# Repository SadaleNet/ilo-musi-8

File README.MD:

**(English: Scroll down for English | toki ike Inli li lon anpa pi toki pona)**

* lipu: https://ilomusi8.sadale.net/
* sitelen tawa lon ilo Jutu "Youtube": (TODO: tenpo ni la ona li lon ala. o awen a!)

# ilo musi 8 - ilo musi pi nasin CHIP-8

kepeken ilo musi 8 (ilo musi ali) la sina ken musi e musi CHIP-8. ilo musi 8 la:

* nasin CHIP-8 ni li ken:
	* nasin CHIP-8 (VIP) li ken
	* nasin SuperCHIP li ken
	* nasin XO-CHIP li ken lili. ni li ken ala: toki `plane n` (kule) en ma sona >= 4096. ali ante li ken
* tenpo pali: 5400 ips (90 instructions/frame)
* nena: nena CHIP-8 ali li lon (0-9, A-F). nena namako X kin li lon
* suli poki: 135x70x24mm
* wawa: poki wawa AAx2 anu linja wawa "USB MicroB"
* sona musi: kepeken lipu sona "TF Card"
	* nasin FAT16 en nasin FAT32 taso (o kepeken ala nasin exFAT!)
	* [nasin nimi "8.3 filename"](https://en.wikipedia.org/wiki/8.3_filename) taso
	* sina kin li ken pana e sona sin tawa ilo musi 8 kepeken lipu sona "TF Card"
* musi open li lon. sina pana e wawa tawa ilo musi 8 sina la sina ken lukin e sitelen pi wile sina
* toki mute li lon: toki pona (sitelen Lasin en sitelen pona) en [sitelen Sate](https://sadale.net/tok/sitelen-sate) en toki ike Inli
* sona ali ona li lon. jan ali li ken lukin e ona li ken ante e ona li ken pali e ona
* jan li ken pali e ona mute kepeken mani lili kepeken tenpo lili (sina pali e ona mute "20" la sina o pana e mani "$12x20" o kepeken tenpo "30minutesx20")
* jan li ken ante e lukin ona (jan li ken ante e musi open. jan li ken ante e sitelen lon selo.)

## sona seme li lon?

```
assembly/        # lon ma ni la sina kama sona e nasin pali pi ilo musi 8
bootloader/      # kepeken sona ni la sina ken pana e sona sin tawa ilo musi 8. ona li kama sona tan ILOMUSI8.BIN lon lipu sona
docs-assets/     # sitelen pi lipu README.MD
enclosure/       # sitelen pi lupa selo
firmware/        # kepeken sona ni la ilo musi 8 li pali. sina ken musi kepeken ilo musi 8 tan ni: sona ni li lon
kicad/           # lipu kiwen sona. ilo musi 8 li jo e lipu kiwen. jan li pana e sona tawa ona la ilo musi 8 li ken pali
label/           # sitelen selo en sitelen poki
manual/          # jan li lukin e ona la jan ni li kama sona e ilo musi 8 li ken musi kepeken ona
```

## o esun e ilo ni!

sina ken esun e ona lon [esun Sate](https://esun.sadale.net/)!

mi jo e mani namako la mi wile pana e ilo musi 8 tawa jan pi mani ala. :)

## o pali e ilo ni!

o lukin e lipu ni: "[assembly/](./assembly/)"

## ken

lipu anpa ni li mi ala. sina wile lukin e ken ona la o lukin e nimi insa ona:

* ./bootloader/linker_script
* ./bootloader/pff3a
* ./firmware/fatfs

mi pali e lipu ante ali. ken ona li ken "BSD 2-clause".

# ilo musi 8 - Handheld CHIP-8 Game Console

ilo musi 8 is a production-ready handheld CHIP-8 game console. Feature list:

* CHIP-8 Compatibility:
	* CHIP-8 (VIP): Full support
	* SuperCHIP: Full support
	* XO-CHIP: Partial support. No support for `plane n` (color mode) and memory beyond 4K. Everything else (e.g. audio) is fully supported
* Performance: 5400 ips (90 instructions/frame)
* Buttons: Full CHIP-8 button support (0-9, A-F), with an extra X key for escaping
* Dimensions: 135x70x24mm
* Power: AAx2 or USB MicroB
* Game Storage: TF card
	* Supports FAT16 and FAT32 (No support for exFAT)
	* Supports [8.3 filename](https://en.wikipedia.org/wiki/8.3_filename) only
	* Firmware update is supported via the card
* Bootrom support. Can be used for showing boot screen upon powering on of the device
* Multi-language UI: English, [Toki Pona](https://en.wikipedia.org/wiki/Toki_Pona) and [Sadalian Script](https://sadale.net/en/sadalian)
* Fully open source, including electronics, enclosure and firmware, with full BOM and assembly instruction.
* Optimized for small scale production in terms of material cost and box build assembly time (At batch of 20, it costs $12 and 30 minutes of assembly time per unit)
* Optimized for white-labeling (custom boot screen via the bootrom, custom branding sticker on enclosure, custom cardboard label, etc.)

## Repo Structure

```
assembly/        # Assembly instruction for you to build your own unit
bootloader/      # Bootloader for flashing the file "ILOMUSI8.BIN" on TF card as firmware
cardboard_label/ # Label slapped onto the packaging cardboard
docs-assets/     # Images for README.MD
enclosure/       # CNC hole-drilling diagram of an off-the-shelf enclosure
firmware/        # Firmware source code
kicad/           # Electronics design
label/           # Keycap labels and branding labels slapped onto the enclosure and cardboard label
manual/          # User manual source and PDF
```

## Ordering a unit

If you speak Toki Pona, it's available via [esun Sate](https://esun.sadale.net/). Please don't order there if you don't speak the language.

I'm also selling/gifting white-labeled units in a few other communities that I care about in small quantities.

This is a hobbyist project. It's all about sharing. Profit-making is not my objective. I intentionally limit my scale of operation to avoid burn out.
Currently I don't have a plan to sell it to the mass public and I'm not sure on if there's even a demand for that.

If you want a unit very badly, you can contact me and tell me your situation. I'll see if I could arrange something for you.

## Building your Own Unit

Please follow the the instruction in the "[assembly/](./assembly/)" folder

# License

This repo contains third-party source code. I do not claim the ownership of these third-party files. Please refer to the license file on the corresponding folders for their licenses:

* ./bootloader/linker_script
* ./bootloader/pff3a
* ./firmware/fatfs

For all other files, I made them. They're released under BSD 2-clause license.

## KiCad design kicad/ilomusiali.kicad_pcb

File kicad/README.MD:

**(English: Scroll down for English | toki ike Inli li lon anpa pi toki pona)**

# lipu kiwen sona

ma ni li jo e sona pi lipu kiwen. mi pali e ona kepeken ilo "KiCad" en ilo lili "[Fabrication-Toolkit](https://github.com/bennymeg/Fabrication-Toolkit)".

sina ken esun e lipu kiwen sona kepeken nasin ni:

1. o open e lipu `ilomusiali-production.zip`
2. insa lipu `ilomusiali-production.zip` la o pana e ni tawa tomo pali: lipu `ilomusiali.zip` li lipu "gerber". lipu `bom.csv` en lipu `positions.csv` li lipu "SMT". mi kepeken tomo pali "JLCPCB".
3. o pana e mani tawa tomo pali. ni la sina o awen. lipu kiwen sona li jo e ijo mute. taso ilo sitelen en ilo kalama li lon ala.
4. o sona e ni: ilo kalama en ilo sitelen li lon ala. o pana e ona kepeken nasin insa [ma ni](../assembly/).

# PCBA Source and Production Files

This folder contains the source and production files for the PCBA. It uses KiCad with production files generated with the plugin "[Fabrication-Toolkit](https://github.com/bennymeg/Fabrication-Toolkit)".

To order PCBA on your own:

1. Extract `ilomusiali-production.zip`
2. Inside the extracted files, send `ilomusiali.zip` as gerber. `bom.csv` and `positions.csv` as SMT files. I used JLCPCB for the PCBA.
3. Pay up and wait for delivery. The PCBA has all electronic parts except for the screen and the buzzer, which you need to put that on your own.
4. Please notice that the buzzer and LCD aren't included. You need to put it on on your own as shown in the [assembly instruction here](../assembly/)

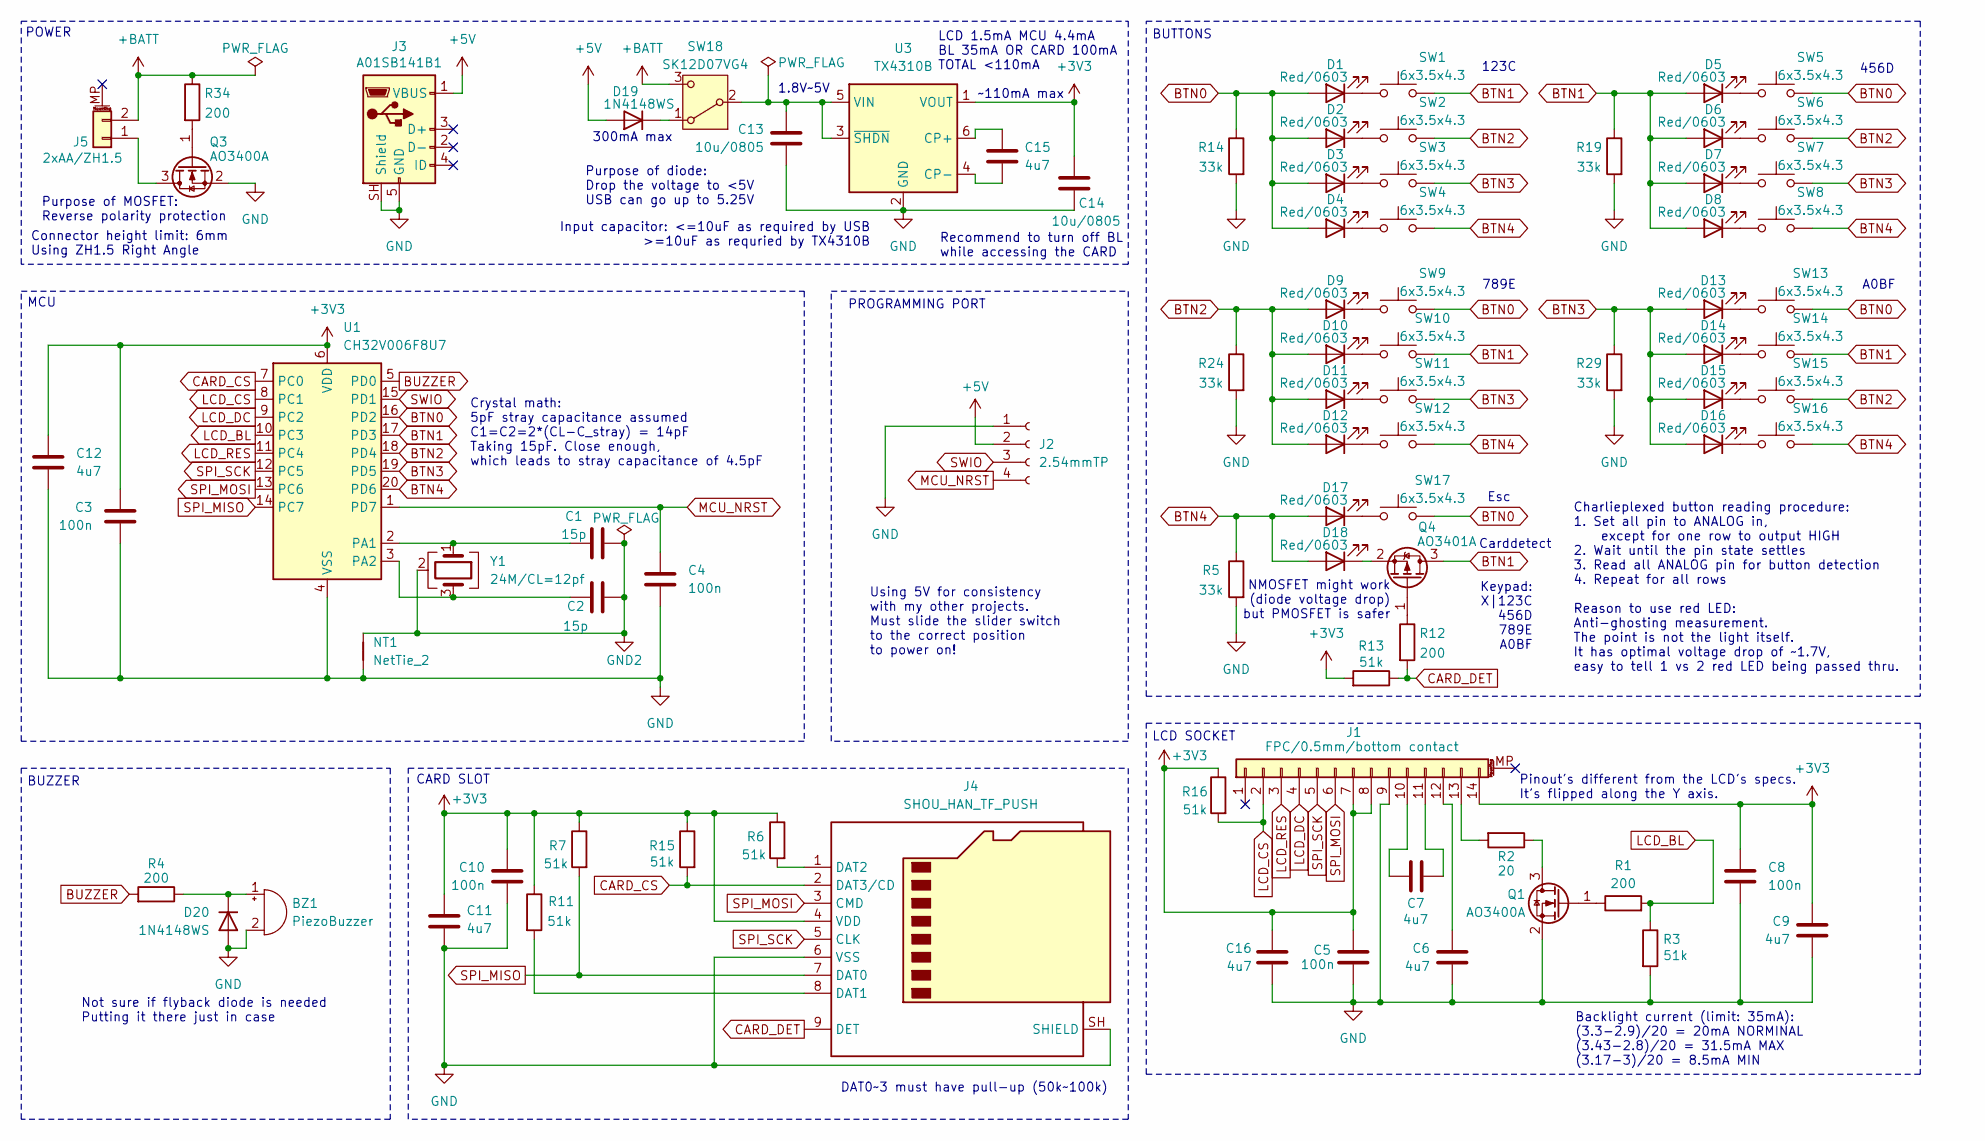
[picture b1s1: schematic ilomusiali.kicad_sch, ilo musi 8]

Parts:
BZ1: PiezoBuzzer; SolderWire-0.1sqmm_1x02_P3.6mm_D0.4mm_OD1mm_Relief
C1, C2: 15p; C_0603_1608Metric; LCSC C1644
C3, C4, C5, C8, C10: 100n; C_0603_1608Metric; LCSC C14663
C6, C7, C9, C11, C12, C15, C16: 4u7; C_0603_1608Metric; LCSC C19666
C13, C14: 10u/0805; C_0805_2012Metric; LCSC C15850
D1, D2, D3, D4, D5, D6, D7, D8, D9, D10, D11, D12, D13, D14, D15, D16, D17, D18: Red/0603; LED_0603_1608Metric; LCSC C2286
D19, D20: 1N4148WS; D_SOD-323; LCSC C2128
J1: FPC/0.5mm/bottom contact; Jushuo_AFC01-S14FCx-00_14P_P0.50mm_Horizontal; LCSC C577443
J2: 2.54mmTP; PinHeader_1x04_P2.54mm_Vertical
J3: A01SB141B1; USB_Micro-B_A01SB141B1-067; LCSC C404969
J4: SHOU_HAN_TF_PUSH; LCSC C393941
J5: 2xAA/ZH1.5; JST_ZH_S2B-ZR-SM4A-TF_1x02-1MP_P1.50mm_Horizontal; LCSC C2681533
NT1: NetTie_2; NetTie-2_SMD_Pad0.2mm
Q1, Q3: AO3400A; SOT-23; LCSC C20917
Q4: AO3401A; SOT-23; LCSC C15127
R1, R4, R12, R34: 200; R_0603_1608Metric; LCSC C8218
R2: 20; R_0603_1608Metric; LCSC C22950
R3, R6, R7, R11, R13, R15, R16: 51k; R_0603_1608Metric; LCSC C23196
R5, R14, R19, R24, R29: 33k; R_0603_1608Metric; LCSC C4216
SW1, SW2, SW3, SW4, SW5, SW6, SW7, SW8, SW9, SW10, SW11, SW12, SW13, SW14, SW15, SW16, SW17: 6x3.5x4.3; ZX-QC36-4.3TPWD; LCSC C7470221
SW18: SK12D07VG4; SW_Slide_SPDT_Angled_CK_OS102011MA1Q; LCSC C393937
U1: CH32V006F8U7; QFN-20-1EP_3x3mm_P0.4mm_EP1.65x1.65mm; LCSC C55112440
U3: TX4310B; SOT-23-6; LCSC C448640
Y1: 24M/CL=12pf; Crystal_SMD_3225-4Pin_3.2x2.5mm; LCSC C362340

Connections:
+3V3: C3.1, C5.1, C8.1, C9.1, C10.1, C11.1, C12.1, C14.1, C16.2, J1.7, J1.8, J1.14, J4.4 (VDD), R6.1, R7.1, R11.1, R13.2, R15.1, R16.1, U1.6 (VDD), U3.1 (VOUT)
+5V: D19.2 (A), J2.2, J3.1 (VBUS)
+BATT: J5.2, R34.1, SW18.3 (C)
BTN0: D1.2 (A), D2.2 (A), D3.2 (A), D4.2 (A), R14.1, SW5.2, SW9.2, SW13.2, SW17.2, U1.16 (PD2)
BTN1: D5.2 (A), D6.2 (A), D7.2 (A), D8.2 (A), Q4.3 (D), R19.1, SW1.2, SW10.2, SW14.2, U1.17 (PD3)
BTN2: D9.2 (A), D10.2 (A), D11.2 (A), D12.2 (A), R24.1, SW2.2, SW6.2, SW15.2, U1.18 (PD4)
BTN3: D13.2 (A), D14.2 (A), D15.2 (A), D16.2 (A), R29.1, SW3.2, SW7.2, SW11.2, U1.19 (PD5)
BTN4: D17.2 (A), D18.2 (A), R5.1, SW4.2, SW8.2, SW12.2, SW16.2, U1.20 (PD6)
BUZZER: R4.2, U1.5 (PD0)
CARD_CS: J4.2 (DAT3/CD), R15.2, U1.7 (PC0)
CARD_DET: J4.9 (DET), R12.2, R13.1
GND: BZ1.2 (-), C3.2, C4.2, C5.2, C6.2, C8.2, C9.2, C10.2, C11.2, C12.2, C13.2, C14.2, C16.1, D20.2 (A), J1.9, J2.1, J3.5 (GND), J3.SH (Shield), J4.6 (VSS), J4.SH (SHIELD), NT1.1, Q1.2 (S), Q3.2 (S), R3.2, R5.2, R14.2, R19.2, R24.2, R29.2, U1.4 (VSS), U1.21 (VSS), U3.2 (GND)
GND2: C1.1, C2.2, NT1.2, Y1.2 (G), Y1.4 (G)
LCD_BL: R1.2, R3.1, U1.10 (PC3)
LCD_CS: J1.2, R16.2, U1.8 (PC1)
LCD_DC: J1.4, U1.9 (PC2)
LCD_RES: J1.3, U1.11 (PC4)
MCU_NRST: C4.1, J2.4, U1.1 (PD7)
unnamed: BZ1.1 (+), D20.1 (K), R4.1
unnamed: D1.1 (K), SW1.1
unnamed: D2.1 (K), SW2.1
unnamed: D3.1 (K), SW3.1
unnamed: D4.1 (K), SW4.1
unnamed: D5.1 (K), SW5.1
unnamed: D6.1 (K), SW6.1
unnamed: D7.1 (K), SW7.1
unnamed: D8.1 (K), SW8.1
unnamed: D9.1 (K), SW9.1
unnamed: D10.1 (K), SW10.1
unnamed: D11.1 (K), SW11.1
unnamed: D12.1 (K), SW12.1
unnamed: D13.1 (K), SW13.1
unnamed: D14.1 (K), SW14.1
unnamed: D15.1 (K), SW15.1
unnamed: D16.1 (K), SW16.1
unnamed: D17.1 (K), SW17.1
unnamed: D18.1 (K), Q4.2 (S)
unnamed: D19.1 (K), SW18.1 (A)
unnamed: C7.1, J1.10
unnamed: C7.2, J1.11
unnamed: C6.1, J1.12
unnamed: J1.13, R2.2
unnamed: J4.8 (DAT1), R11.2
unnamed: J4.1 (DAT2), R6.2
unnamed: J5.1, Q3.3 (D)
unnamed: Q1.3 (D), R2.1
unnamed: Q1.1 (G), R1.1
unnamed: Q3.1 (G), R34.2
unnamed: Q4.1 (G), R12.1
unnamed: C13.1, SW18.2 (B), U3.3 (~SHDN), U3.5 (VIN)
unnamed: C1.2, U1.2 (PA1), Y1.1
unnamed: C2.1, U1.3 (PA2), Y1.3
unnamed: C15.1, U3.6 (CP+)
unnamed: C15.2, U3.4 (CP-)
SPI_MISO: J4.7 (DAT0), R7.2, U1.14 (PC7)
SPI_MOSI: J1.6, J4.3 (CMD), U1.13 (PC6)
SPI_SCK: J1.5, J4.5 (CLK), U1.12 (PC5)
SWIO: J2.3, U1.15 (PD1)

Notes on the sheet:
PROGRAMMING PORT
MCU
Charlieplexed button reading procedure: 1. Set all pin to ANALOG in, except for one row to output HIGH 2. Wait until the pin state settles 3. Read all ANALOG pin for button detection 4. Repeat for all rows Reason to use red LED: Anti-ghosting measurement. The point is not the light itself. It has o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
Connector height limit: 6mm Using ZH1.5 Right Angle
Keypad: X|123C 456D 789E A0BF
456D
NMOSFET might work (diode voltage drop) but PMOSFET is safer
Not sure if flyback diode is needed Putting it there just in case
Pinout's different from the LCD's specs. It's flipped along the Y axis.
Recommend to turn off BL while accessing the CARD
789E
Backlight current (limit: 35mA): (3.3-2.9)/20 = 20mA NORMINAL (3.43-2.8)/20 = 31.5mA MAX (3.17-3)/20 = 8.5mA MIN
LCD SOCKET
Crystal math: 5pF stray capacitance assumed C1=C2=2*(CL-C_stray) = 14pF Taking 15pF. Close enough, which leads to stray capacitance of 4.5pF
Using 5V for consistency with my other projects. Must slide the slider switch to the correct position to power on!
CARD SLOT
Purpose of diode: Drop the voltage to <5V USB can go up to 5.25V
Carddetect
Purpose of MOSFET: Reverse polarity protection
LCD 1.5mA MCU 4.4mA BL 35mA OR CARD 100mA TOTAL <110mA
1.8V~5V
Input capacitor: <=10uF as required by USB >=10uF as requried by TX4310B
300mA max
Esc
123C
BUTTONS
POWER
~110mA max
BUZZER
A0BF
DAT0~3 must have pull-up (50k~100k)

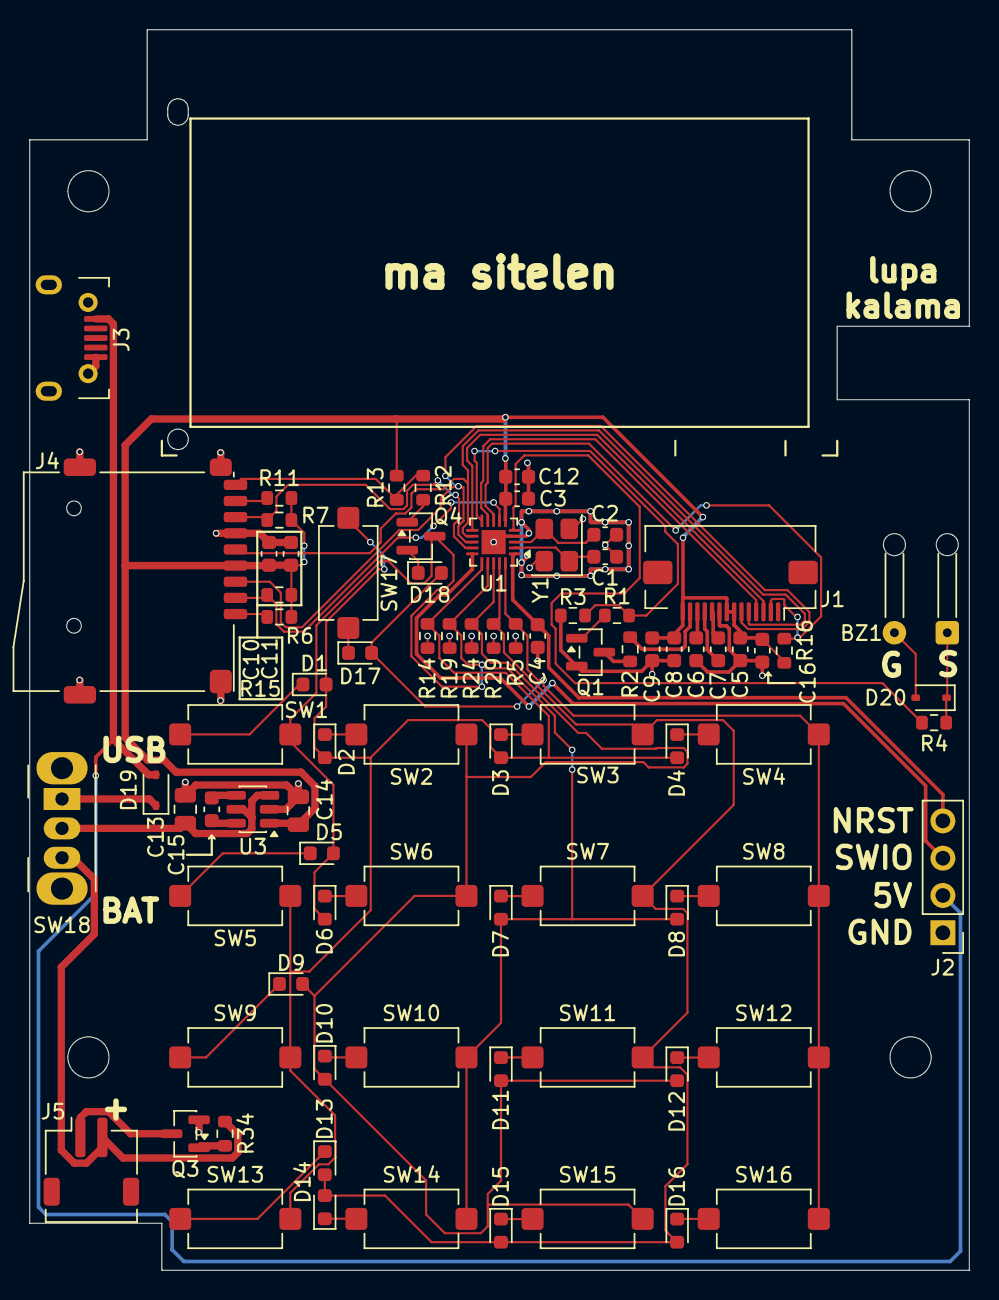
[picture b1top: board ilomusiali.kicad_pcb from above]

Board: 2 copper layers, 64.0 x 84.5 mm, 84 parts (0 on the bottom side), 58 nets.

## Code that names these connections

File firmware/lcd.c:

// Copyright 2026 Wong Cho Ching <https://sadale.net>
//
// Redistribution and use in source and binary forms, with or without
// modification, are permitted provided that the following conditions
// are met:
//
// 1. Redistributions of source code must retain the above copyright
// notice, this list of conditions and the following disclaimer.
//
// 2. Redistributions in binary form must reproduce the above copyright
// notice, this list of conditions and the following disclaimer in the
// documentation and/or other materials provided with the distribution.
//
// THIS SOFTWARE IS PROVIDED BY THE COPYRIGHT HOLDERS AND CONTRIBUTORS
// "AS IS" AND ANY EXPRESS OR IMPLIED WARRANTIES, INCLUDING, BUT NOT
// LIMITED TO, THE IMPLIED WARRANTIES OF MERCHANTABILITY AND FITNESS FOR
// A PARTICULAR PURPOSE ARE DISCLAIMED. IN NO EVENT SHALL THE COPYRIGHT
// HOLDER OR CONTRIBUTORS BE LIABLE FOR ANY DIRECT, INDIRECT,
// INCIDENTAL, SPECIAL, EXEMPLARY, OR CONSEQUENTIAL DAMAGES (INCLUDING,
// BUT NOT LIMITED TO, PROCUREMENT OF SUBSTITUTE GOODS OR SERVICES; LOSS
// OF USE, DATA, OR PROFITS; OR BUSINESS INTERRUPTION) HOWEVER CAUSED
// AND ON ANY THEORY OF LIABILITY, WHETHER IN CONTRACT, STRICT
// LIABILITY, OR TORT (INCLUDING NEGLIGENCE OR OTHERWISE) ARISING IN
// ANY WAY OUT OF THE USE OF THIS SOFTWARE, EVEN IF ADVISED OF THE
// POSSIBILITY OF SUCH DAMAGE.

#include "adc.h"
#include "lcd.h"

#include "ch32fun.h"
#include <stdbool.h>
#include <stdint.h>

#define PIN_LCD_CS (1)
#define PIN_LCD_DC (2)
#define PIN_LCD_BL (3)
#define PIN_LCD_RES (4)

const uint8_t LCD_REFRESH_SEQUENCE[] = {
	0xE2, // Software RESET
	0xAE, // Display OFF
	0x40, // Set Start Line to 0

	0xA2, // Bias Select 1/9
	0xA1, // SEG Direction reverse
	0xC0, // COM Direction normal

	0x24, // Regulation Ratio = 5 (max is 7)
	//0x81, 0x20, // EV is set in lcd_set_contrast()

	0x2C, // Power Control: Booster on
	0x2E, // Power Control: Regulator on
	0x2F, // Power Control: Follower on
};

#define LCD_DEFAULT_CONTRAST (0x20)
#define LCD_DEFAULT_BACKLIGHT (0)
static uint8_t lcd_contrast; // Range: 0x00..0x3F
static uint8_t lcd_backlight; // Range: 0~15
static bool lcd_backlight_suppressed;

static const uint8_t* lcd_dma_buffer; // CONCURRENCY_VARIABLE: Written in lcd_transfer_begin(), read/written by lcd_transfer_next_row()
static size_t lcd_dma_row_index; // CONCURRENCY_VARIABLE: ditto
static volatile bool lcd_dma_transfer_in_progress; // CONCURRENCY_VARIABLE: Written in lcd_transfer_begin() and DMA1_Channel3_IRQHandler(), read by lcd_is_transfer_in_progress()
static volatile bool lcd_display_config_updated; // CONCURRENCY_VARIABLE: Written in lcd_set_contrast(), lcd_refresh() and DMA1_Channel3_IRQHandler(), read by DMA1_Channel3_IRQHandler()

static void lcd_use_command_mode(void) {
	// LCD CS LOW, DC LOW (select LCD, send command)
	GPIOC->BSHR = ((1<<PIN_LCD_CS)<<16) | ((1<<PIN_LCD_DC)<<16);
}

static void lcd_use_data_mode(void) {
	// LCD CS LOW, DC HIGH (select LCD, send data)
	GPIOC->BSHR = ((1<<PIN_LCD_CS)<<16) | ((1<<PIN_LCD_DC)<<0);
}

static void lcd_use_deselect_mode(void) {
	// LCD CS HIGH
	GPIOC->BSHR = ((1<<PIN_LCD_CS)<<0);
}

static void lcd_spi_send_byte(uint8_t data) {
	while(!(SPI1->STATR & SPI_STATR_TXE)){}
	SPI1->DATAR = data;
	// Wait until completion of transfer.
	// That's because we might want to change the slave select line
	// or other control lines right after calling this function.
	while(SPI1->STATR & SPI_STATR_BSY){}
}

static void lcd_transfer_next_row(void) {
	static uint8_t lcd_dma_buffer_row[DISPLAY_WIDTH];

	// Set page
	lcd_use_command_mode();
	lcd_spi_send_byte(0xb0 | lcd_dma_row_index);
	lcd_spi_send_byte(0x10 | 0);
	lcd_spi_send_byte(0x00 | 4);

	lcd_use_data_mode();
	// Fill in the lcd_dma_buffer_row to be sent via DMA
	for (int i=0; i<DISPLAY_WIDTH; i++) {
		lcd_dma_buffer_row[i] = lcd_dma_buffer[i*DISPLAY_HEIGHT/8+lcd_dma_row_index];
	}

	// write memory barrier to make sure that the content of lcd_dma_buffer_row is updated to the DMA
	asm volatile("fence ow,ow" ::: "memory");
	DMA1_Channel3->MADDR = (uint32_t)lcd_dma_buffer_row; // memory source
	DMA1_Channel3->CNTR = DISPLAY_WIDTH; // number of items to write
	SPI1->CTLR2 |= SPI_CTLR2_TXDMAEN;
	DMA1_Channel3->CFGR |= DMA_CFGR1_EN;
}

void INTERRUPT_DECORATOR DMA1_Channel3_IRQHandler(void) {
	DMA1->INTFCR |= DMA_CTCIF3;
	// Must wait for completion of SPI transfer before changing the LCD control lines
	// DMA SPI TX transfer compelte only look for TXE flag and doesn't wait for BSY flag
	while(SPI1->STATR & SPI_STATR_BSY){}
	DMA1_Channel3->CFGR &= ~DMA_CFGR1_EN;
	SPI1->CTLR2 &= ~SPI_CTLR2_TXDMAEN;

	if(adc_card_has_insert_event()) {
		// Card insertion event detected
		// Aborting LCD rendering immediately!
		lcd_use_deselect_mode();
		lcd_dma_transfer_in_progress = false;
	} else {
		if(++lcd_dma_row_index < DISPLAY_HEIGHT/8) {
			lcd_transfer_next_row();
		} else {
			if(lcd_display_config_updated) {
				lcd_use_command_mode();
				// Set contrast
				lcd_spi_send_byte(0x81);
				lcd_spi_send_byte(lcd_contrast);
				// Turn on display
				lcd_spi_send_byte(0xAF);
				lcd_display_config_updated = false;
			}

			// All done. Deselecting LCD CS
			// Must deselect even if lcd_display_config_updated is false
			// becasue the DMA transfer itself would have selected the LCD CS
			lcd_use_deselect_mode();
			lcd_dma_transfer_in_progress = false;
		}
	}
}

void lcd_init_first_stage(void) {
	// This module owns the following pins: LCD_CS, LCD_DC, LCD_DC, LCD_RES
	// This module also owns the SPI's DMA because the card ain't using it.

	// Enable the GPIO
	RCC->PB2PCENR |= RCC_IOPCEN;

	// Deselect LCD CS
	lcd_use_deselect_mode();

	// GPIO PC1, PC2, PC4 is output PUSH-PULL, PC3 is output ALT PUSH-PULL
	GPIOC->CFGLR &= ~((GPIO_CFGLR_MASK << (4*1)) | (GPIO_CFGLR_MASK << (4*2)) | (GPIO_CFGLR_MASK << (4*3)) | (GPIO_CFGLR_MASK << (4*4)));
	GPIOC->CFGLR |= (GPIO_CFGLR_OUT_PP << (4*1)) | (GPIO_CFGLR_OUT_PP << (4*2)) | (GPIO_CFGLR_OUT_AF_PP << (4*3)) | (GPIO_CFGLR_OUT_PP << (4*4));

	lcd_dma_transfer_in_progress = false;
	lcd_contrast = LCD_DEFAULT_CONTRAST;
	lcd_backlight = LCD_DEFAULT_BACKLIGHT;
	lcd_backlight_suppressed = true;
	lcd_display_config_updated = true;

	Delay_Ms(20); // Wait for power to stabalize (LCD specs recommends >1ms)
	// Toggle LCD RES pin (first set it to LOW, then set it to HIGH)
	GPIOC->BSHR = ((1<<PIN_LCD_RES)<<16);
	Delay_Us(100); // LCD's requirement: >5us
}

void lcd_init_second_stage(void) {
	GPIOC->BSHR = ((1<<PIN_LCD_RES)<<0);
	Delay_Us(100); // LCD's requirement: >5us

	lcd_refresh();
}

void lcd_transfer_begin(const void *buffer) {
	// Wait until completion of the previous LCD DMA transfer
	while(lcd_is_transfer_in_progress()){}

	// Compiler-level barrier for lcd_dma_buffer and lcd_dma_row_index so that the variables wouldn't have to be defined as volatile
	asm volatile("" ::: "memory");
	lcd_dma_buffer = buffer;
	lcd_dma_row_index = 0;
	lcd_dma_transfer_in_progress = true;
	lcd_transfer_next_row();
}

bool lcd_is_transfer_in_progress(void) {
	return lcd_dma_transfer_in_progress;
}

void lcd_refresh(void) {
	// Wait until completion of LCD DMA transfer
	while(lcd_is_transfer_in_progress()){}

	lcd_use_command_mode();
	// Send out the initialization sequence
	for (size_t i=0; i<sizeof(LCD_REFRESH_SEQUENCE)/sizeof(*LCD_REFRESH_SEQUENCE); i++) {
		lcd_spi_send_byte(LCD_REFRESH_SEQUENCE[i]);
	}
	// All done. Deselect LCD CS pin. Please keep in mind that the display would be turned off until
	// the next lcd_transfer_begin() is called and the DMA it kicks off completed the transfer
	lcd_use_deselect_mode();
	lcd_display_config_updated = true;
}

static void lcd_set_brightness_inner(void) {
	TIM1->CH3CVR = lcd_backlight_suppressed ? 0 : lcd_backlight;
}

void lcd_set_brightness(uint8_t value) {
	lcd_backlight = value;
	lcd_set_brightness_inner();
}

void lcd_set_backlight_suppression(bool value) {
	lcd_backlight_suppressed = value;
	lcd_set_brightness_inner();
}

void lcd_set_contrast(uint8_t value) {
	lcd_contrast = value;
	lcd_display_config_updated = true;
}

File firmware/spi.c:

// Copyright 2026 Wong Cho Ching <https://sadale.net>
//
// Redistribution and use in source and binary forms, with or without
// modification, are permitted provided that the following conditions
// are met:
//
// 1. Redistributions of source code must retain the above copyright
// notice, this list of conditions and the following disclaimer.
//
// 2. Redistributions in binary form must reproduce the above copyright
// notice, this list of conditions and the following disclaimer in the
// documentation and/or other materials provided with the distribution.
//
// THIS SOFTWARE IS PROVIDED BY THE COPYRIGHT HOLDERS AND CONTRIBUTORS
// "AS IS" AND ANY EXPRESS OR IMPLIED WARRANTIES, INCLUDING, BUT NOT
// LIMITED TO, THE IMPLIED WARRANTIES OF MERCHANTABILITY AND FITNESS FOR
// A PARTICULAR PURPOSE ARE DISCLAIMED. IN NO EVENT SHALL THE COPYRIGHT
// HOLDER OR CONTRIBUTORS BE LIABLE FOR ANY DIRECT, INDIRECT,
// INCIDENTAL, SPECIAL, EXEMPLARY, OR CONSEQUENTIAL DAMAGES (INCLUDING,
// BUT NOT LIMITED TO, PROCUREMENT OF SUBSTITUTE GOODS OR SERVICES; LOSS
// OF USE, DATA, OR PROFITS; OR BUSINESS INTERRUPTION) HOWEVER CAUSED
// AND ON ANY THEORY OF LIABILITY, WHETHER IN CONTRACT, STRICT
// LIABILITY, OR TORT (INCLUDING NEGLIGENCE OR OTHERWISE) ARISING IN
// ANY WAY OUT OF THE USE OF THIS SOFTWARE, EVEN IF ADVISED OF THE
// POSSIBILITY OF SUCH DAMAGE.

#include "adc.h"
#include "lcd.h"
#include "spi.h"

#include "ch32fun.h"

void spi_init(void) {
	// This module owns the following pins: CARD_CS, SCK, MOSI, MISO
	// Keep in mind that, in particular, LCD_CS is owned by the lcd module, and that
	// the SPI DMA isn't being owned by this module because only LCD uses it.

	// Enable the GPIO
	RCC->PB2PCENR |= RCC_IOPCEN;

	// Reset SPI
	RCC->PB2PRSTR |= RCC_SPI1RST;
	RCC->PB2PRSTR &= ~RCC_SPI1RST;
	// Enable the SPI clock source
	RCC->PB2PCENR |= RCC_SPI1EN;

	// Reset SPI
	RCC->PB2PRSTR |= RCC_SPI1RST;
	RCC->PB2PRSTR &= ~RCC_SPI1RST;
	// Enable the SPI clock source
	RCC->PB2PCENR |= RCC_SPI1EN;

	// Configure SPI. SPI_Mode_Master and SPI_CTLR1_SPE must be set after CS pin is high
	SPI1->CTLR1 =	SPI_CTLR1_BR_2 | SPI_CTLR1_BR_1 | SPI_CTLR1_BR_0 // Same as lcd_spi_set_mode(SPI_MODE_MEMORY_CARD_SLOW)
					| (SPI_CPOL_Low | SPI_CPHA_1Edge) // SPI Mode 0 (That's for the card. LCD requires SPI mode 3 instead (SPI_CPOL_High | SPI_CPHA_2Edge))
					| SPI_NSS_Soft // Software NSS mode
					| SPI_Mode_Master // Master mode
					| 0 // (lack of SPI_CTLR1_DFF) 8bit mode
					| SPI_Direction_2Lines_FullDuplex // Use both MOSI and MISO
					| SPI_CTLR1_SPE; // SPI begin!

	// Enable DMA (other component may also enable DMA on their own. No harm to enable it multiple times.)
	RCC->HBPCENR |= RCC_DMA1EN;

	// Configure DMA for SPI TX
	DMA1_Channel3->PADDR = (uint32_t)(&SPI1->DATAR); // Peripheral address register

	DMA1_Channel3->CFGR =
		// (Not specifying DMA_CFGR1_PL) Set the priority to "Low"
		// (Not specifying DMA_CFGR1_PSIZE) 8bit data for peripheral
		// (Not specifying DMA_CFGR1_MSIZE) 8bit data for memory
		DMA_CFGR1_MINC | // Incrememt memory address
		DMA_CFGR1_DIR | // Read from memory, write to peripheral
		DMA_CFGR1_TCIE; // Enable transfer-complete interrupt

	// Configure interrupt controller
	DMA1->INTFCR |= DMA_CTCIF3; // Clear the transfer-complete interrupt flag for SPI TX, just in case.
	PFIC->IPRIOR[DMA1_Channel3_IRQn] = 0x80; // The priority is 0x80 (the highest but that it can be preempted)

	// Configure DMA for SPI RX
	DMA1_Channel2->PADDR = (uint32_t)(&SPI1->DATAR); // Peripheral address register
	DMA1_Channel2->CFGR =
		(DMA_CFGR1_PL_1|DMA_CFGR1_PL_0) | // Set the priority to "Very High"
		// (Not specifying DMA_CFGR1_PSIZE) 8bit data for peripheral
		// (Not specifying DMA_CFGR1_MSIZE) 8bit data for memory
		DMA_CFGR1_MINC; // Incrememt memory address
		// (Not spedifying DMA_CFGR1_DIR) Read from peripheral, write to memory


	// Card CS pin is P0
	// SPI pins are PC5 SCK, PC6 MOSI, and PC7 MISO
	GPIOC->CFGLR &= ~((GPIO_CFGLR_MASK << (4*0)) | (GPIO_CFGLR_MASK << (4*5)) | (GPIO_CFGLR_MASK << (4*6)) | (GPIO_CFGLR_MASK << (4*7)));
	GPIOC->CFGLR |= (GPIO_CFGLR_OUT_PP << (4*0)) | (GPIO_CFGLR_OUT_AF_PP << (4*5)) | (GPIO_CFGLR_OUT_AF_PP << (4*6)) | (GPIO_CFGLR_IN_FLOAT << (4*7));

	spi_set_mode(SPI_MODE_MEMORY_CARD_SLOW);
}

void spi_send_byte(uint8_t data) {
	while(!(SPI1->STATR & SPI_STATR_TXE)){}
	SPI1->DATAR = data;
	// Wait until completion of transfer.
	// That's because we might want to change the slave select line
	// or other control lines right after calling this function.
	while(SPI1->STATR & SPI_STATR_BSY){}
}

void spi_set_mode(enum spi_mode mode) {
	// Always wait until LCD transfer completion
	// even if we're switching to SPI_MODE_LCD.
	// That's because a switch from SPI_MODE_LCD to SPI_MODE_LCD
	// would still cause disruption to the SPI bus
	while(lcd_is_transfer_in_progress()){}

	switch(mode) {
		case SPI_MODE_LCD:
			lcd_set_backlight_suppression(false);
			// Go back to LCD mode (mode 3)
			//SPI1->CTLR1 &= ~(SPI_CPOL_High | SPI_CPHA_2Edge); // redundant because we're gonna use |=
			SPI1->CTLR1 |= (SPI_CPOL_High | SPI_CPHA_2Edge);

			// LCD max 20Mhz
			// Setting the divider to 4. That'd be 48Mhz/4 = 12Mhz.
			SPI1->CTLR1 &= ~SPI_CTLR1_BR;
			SPI1->CTLR1 |= SPI_CTLR1_BR_0;

			// PFIC: Enable interrupt for DMA1_Channel3_IRQn (SPI TX, used by LCD)
			DMA1->INTFCR |= DMA_CTCIF3; // Clear the transfer-complete interrupt flag so that the interrupt handler won't get misfired right away
			DMA1_Channel3->CFGR |= DMA_CFGR1_TCIE;
			PFIC->IENR[DMA1_Channel3_IRQn/32] |= (1<<(DMA1_Channel3_IRQn%32));
		break;
		case SPI_MODE_MEMORY_CARD:
		case SPI_MODE_MEMORY_CARD_SLOW:
			lcd_set_backlight_suppression(true);
			SPI1->DATAR; // Clear the RX byte

			// PFIC: Disable interrupt for DMA1_Channel3_IRQn (SPI TX, used by LCD)
			PFIC->IRER[DMA1_Channel3_IRQn/32] |= (1<<(DMA1_Channel3_IRQn%32));
			DMA1_Channel3->CFGR &= ~DMA_CFGR1_TCIE;

			// Switch to SPI mode 0 for memory card
			SPI1->CTLR1 &= ~(SPI_CPOL_High | SPI_CPHA_2Edge);

			if(mode == SPI_MODE_MEMORY_CARD) {
				// Card max 25Mhz
				// Setting the divider to 2. That'd be 48Mhz/2 = 24Mhz
				SPI1->CTLR1 &= ~SPI_CTLR1_BR;
			} else { // mode == SPI_MODE_MEMORY_CARD_SLOW
				// Required data rate for card: 100kHz ~ 400kHz
				// Setting the divider to 256. That'd be 48Mhz/256 = 187kHz
				// SPI1->CTLR1 &= ~SPI_CTLR1_BR; // Commenting out. Redundant.
				SPI1->CTLR1 |= SPI_CTLR1_BR_2 | SPI_CTLR1_BR_1 | SPI_CTLR1_BR_0;
			}
		break;
	}
}

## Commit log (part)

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2026-02-08 Initial commit with schematics draft
2026-02-11 electronics: Fixed a few bugs, including battery polarity protection bug, using a better diode, lowered USB serial resistor's value and fixed potential short circuit condition in case the Esc button 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
2026-02-21 electronics: Made first draft of component placement
2026-03-11 electronics: Completed layout for PCB rev0
2026-03-11 electronics: PCB rev0: Enlarged the LCD mounting holes to account for tolerance. This is the PCB rev0 sent for manufacturing
2026-03-29 bootloader: Initial commit. All feature has been implemented and briefly tested
2026-04-03 enclosure: First commit. This is the design I sent for first prototype manufacturing
2026-04-03 enclosure: Drawing updated for clearing up ambiguity. This was never sent to the manufacturer I'm using.
    The way to manufacture this enclosure is to purchase an
    off-the-shelf enclosure and ask the manufacturer to CNC-mill it.
    The previous version of the enclosure drawing was ambigious and
    it got manufactured incorrectly. The side holes were shifted downward by 1mm.
    I communicated with the manufacturer and they agreed to shift the
    holes back upward by 1mm. They told me not to send them a new drawing.
2026-04-03 enclosure_label: Added key label for the enclosure
2026-05-15 firmware: Implemented all ADC features, including button driver, card prescence detection and supply voltage detection
2026-05-21 adc: Fixed card insert detection bug; Make it configure the DMA count after configuring the address; Reset ADC on initialization
2026-05-22 bootloader: Corrected comments
2026-05-22 lcd: Initial commit with minimal usable DMA handling
2026-05-22 bootloader: Fixed SPI handling (a hidden bug that I didn't discover)
2026-05-22 chip8: Integrated chip8 emulator and got the first game working
2026-05-22 lcd: Implemented lcd_set_contrast(). Also extracted commonly used GPIO manipulation functions
2026-05-22 lcd: Implemented lcd_set_brightness() for setting the backlight brightness
2026-05-24 buzzer: Implemented with volume adjustment mechanism; tim1_pwm: extracted into a dedicated file; chip8: Implemented audio handling and vblank wait handling
2026-05-29 buzzer: Added another workaround of improper ch32fun definition
2026-05-29 adc: Exposes card insertion and removal events; Fixed GPIOD configuration handling that it mistakenly modified the NRST and SWIO pin's config
2026-05-29 spi/memorycard/lcd: Implemented memory card driver. Also refactored lcd driver so that the SPI can be shared between the memory card and the LCD
2026-05-30 chip8: Removed a useless include
2026-05-30 buzzer: fixed click sound on boot by initializing the buffer before kicking off the DMA
2026-05-30 lcd/spi: Implemented turning off backlight upon accessing the memory card. This is for reducing the peak power usage to make thing with specs of the power supply
2026-06-01 draw: Implemented drawing functions. Also implemented first version of the font
2026-06-03 bootloader: Enabled FAT16 support (in addition to the existing FAT32 support)
2026-06-03 file: Implemented file_load_rom() except for ini quirk file handling. Briefly tested OK
2026-06-04 ui: Implemented minimal game selection menu
2026-06-06 ui: Bugfix on directory navigation: prevents selecting non-existant entries; fixed loading ROM on non-root directory
2026-06-06 file: Moved mounting mechanism from spi module to the file module. Also exposes the f_mount() error in case the card hadn't been initialized properly
2026-06-06 ui: Implemented card error screen
2026-06-07 chip8: Corrected FX29 / FX30 implementation
2026-06-07 chip8: audio buffer now uses uint8_t so that all configurable buffer becomes uint8_t. This change also fixes the buzzer audio playback distortion bug
2026-06-07 ui: Implemented INI config file loader/parser (happy path working. other scenarios to be tested)
2026-06-10 ui: Implemented config INI file screen UI. However, functionality of saving INI and flashing to boot ROM hasn't been implemented yet
2026-06-11 ui/file: Implemented actual config saving mechanism in file_save_config()
2026-06-11 file: Reduced default buzzer audio frequency from 1000Hz to 500Hz
2026-06-12 ui/file: Added previous missing bulkmem.h
2026-06-12 ui: Added legends to game selection menu; Fixed empty screen bug when opening empty directory
2026-06-14 ui: Implemented display of gameplay control of each game; Also removed some redundant anti-tearing handling (because the LCD response time is slow anyway so any tearing won't be visible)
2026-06-14 Comment clarification for my modification on fatfs
2026-06-17 bulkmem: Removed menu_current_dir from bulkmem because the path's required for loading the CHIP8 ROM. This piece of memory must not be shared
2026-06-18 ui: Implemented game over screen and game crash screen
2026-06-18 ui: Extracted main loop code into multiple functions naming screen_xxx_handler() to make the purpose of the switch-case in the main loop more obvious
2026-06-19 bootloader: Changed the firmware upgrade filename to ILOMUSI8.BIN
2026-06-19 file: Avoids modifying the FRESULT enum. Instead, extends it
2026-06-19 ui: Implemented automatic firwmare verification mechanism on boot. Also delete the firmware file upon successful verification (so that the firmware update won't be performed again in the bootloader)
2026-06-19 bootloader: Improved card reading performance by raising the clock rate to 3Mhz after initialization. It helps reducing the boot time when the card has too many files in the root directory
2026-06-19 ui: Added path length check and excessive path length handling
2026-06-20 file: Implemented storage flag saving and loading. Also fixed a storage flag handling bug in the CHIP-8 emulator
2026-06-20 file: Reduced fisk of file corruption by adding an f_sync() while writing INI file to the card
2026-06-20 ui: Game config UI title minor change. s/CONFIG INI <FILENAME>/CONFIG <FILENAME>/
2026-06-20 bootloader: reviewed function parameters and improved accordingly
2026-06-21 config, flash: First draft of global config saving mechanism. Found to be quite unreliable. Further debug needed
2026-06-24 config, flash: Stops programming the same cell multiple times because the customer support of CH32V006 recommended against that. Config storage algorithm adjusted accordingly
2026-06-24 bootloader: Rebuilt with a newer version of compiler
2026-06-26 ui: Implemented global config screen (except for boot rom handling). Also slightly adjusted text position of game config screen
2026-06-27 file: Added INI config for replay button
2026-06-28 font: added replay button that I missed in the previous commit
2026-06-28 bulkmem: Defined FILE_BUFFER_SIZE for each of referral to the buffer size
2026-06-28 file/ui: Implemented filelist caching and sorting mechanism
2026-06-28 file: Improved qsort algorithm by utilizing memmove()
2026-06-29 config: Adjusted default config to a sane value
2026-06-29 file: Changed post-firmware update handling. Instead of deleting the firmware file after success, it renames it
2026-06-29 ui: Corrected INI save error handling by directly jumping to the SCREEN_ERROR (instead of going thru the SCREEN_MENU)
